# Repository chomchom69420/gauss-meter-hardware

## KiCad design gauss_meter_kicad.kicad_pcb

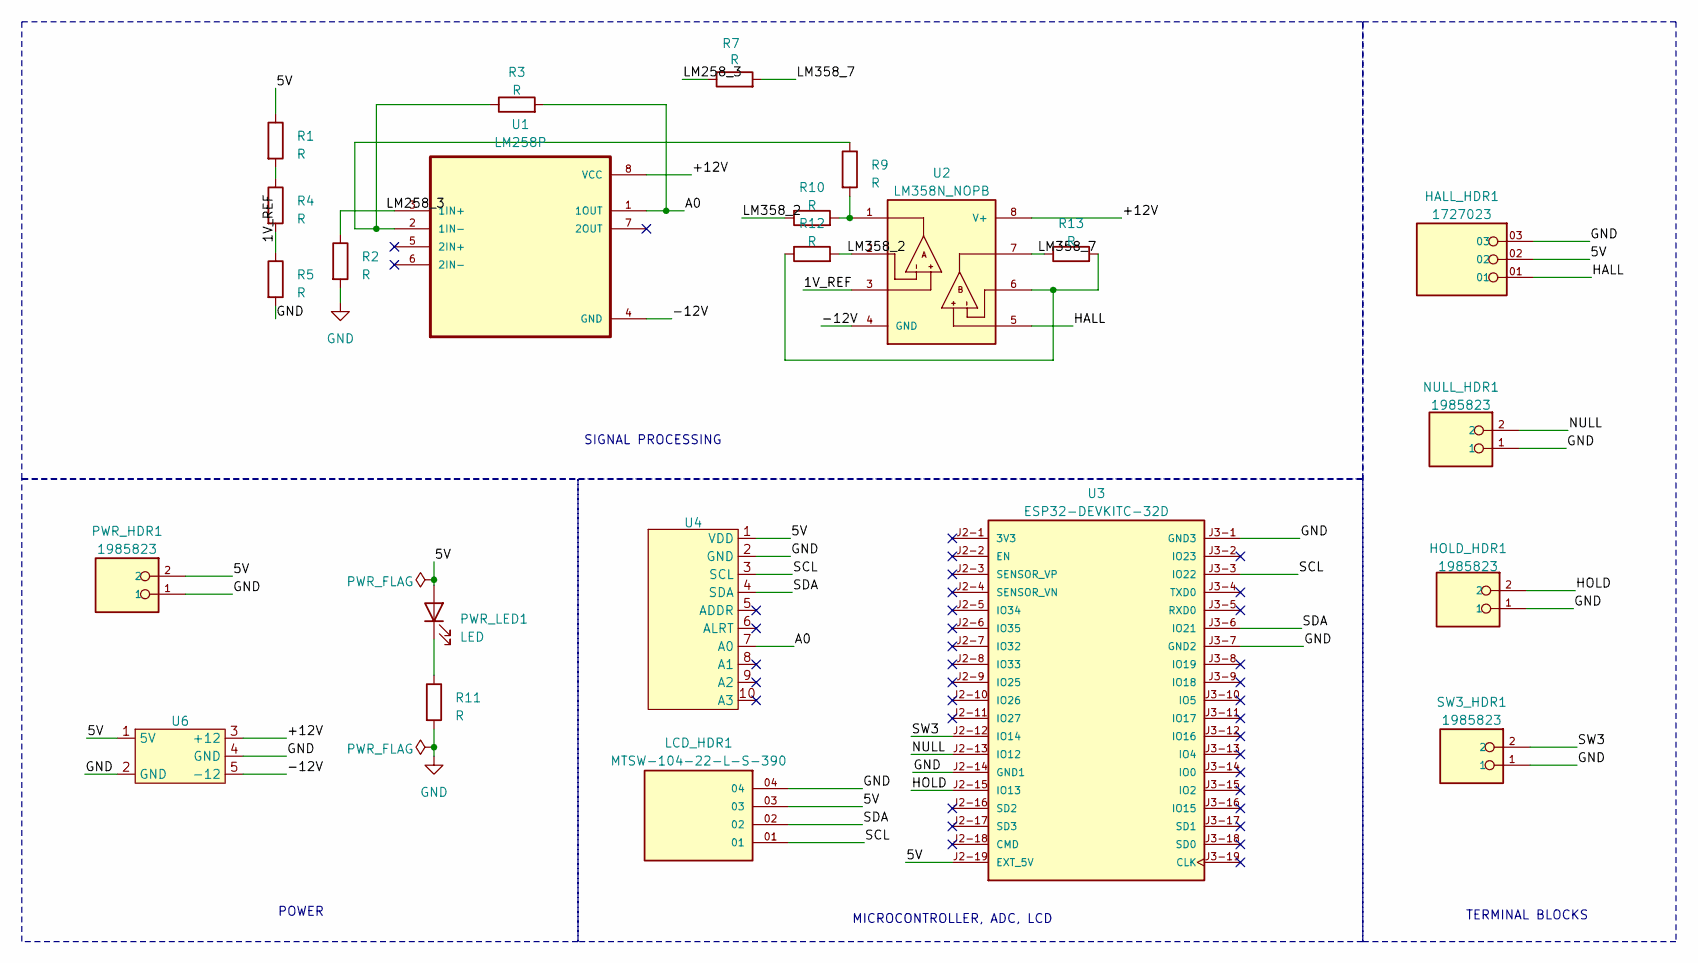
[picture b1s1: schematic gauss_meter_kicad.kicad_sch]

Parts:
HALL_HDR1: 1727023; PHOENIX_1727023; PARTREV 03.03.2021
HOLD_HDR1: 1985823; PHOENIX_1985823; PARTREV 03.03.2021
LCD_HDR1: MTSW-104-22-L-S-390; SAMTEC_MTSW-104-22-L-S-390; PARTREV R
NULL_HDR1: 1985823; PHOENIX_1985823; PARTREV 03.03.2021
PWR_HDR1: 1985823; PHOENIX_1985823; PARTREV 03.03.2021
PWR_LED1: LED; LED_D3.0mm_Horizontal_O1.27mm_Z2.0mm
R1, R2, R3, R4, R5, R7, R9, R10, R11, R12, R13: R; R_gauss_custom
SW3_HDR1: 1985823; PHOENIX_1985823; PARTREV 03.03.2021
U1: LM258P; DIP794W45P254L959H508Q8
U2: LM358N_NOPB; DIP794W45P254L959H508Q8
U3: ESP32-DEVKITC-32D; MODULE_ESP32-DEVKITC-32D; PARTREV V4
U4: ads1115
U6: DUAL_BOOST_5_12

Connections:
/1V_REF: R4.2, R5.1, U2.3
/5V: HALL_HDR1.02, LCD_HDR1.03, PWR_HDR1.2, PWR_LED1.2 (A), R1.1, U3.J2-19 (EXT_5V), U4.1 (VDD), U6.1 (5V)
/+12V: U1.8 (VCC), U2.8 (V+), U6.3 (+12)
/-12V: U1.4 (GND), U2.4 (GND), U6.5 (-12)
/A0: R3.2, U1.1 (1OUT), U4.7 (A0)
/HALL: HALL_HDR1.01, U2.5
/HOLD: HOLD_HDR1.2, U3.J2-15 (IO13)
/LM258_3: R2.1, R7.1, U1.3 (1IN+)
/LM358_2: R10.1, R12.2, U2.2
/LM358_7: R7.2, R13.1, U2.7
/NULL: NULL_HDR1.2, U3.J2-13 (IO12)
/SCL: LCD_HDR1.01, U3.J3-3 (IO22), U4.3 (SCL)
/SDA: LCD_HDR1.02, U3.J3-6 (IO21), U4.4 (SDA)
/SW3: SW3_HDR1.2, U3.J2-12 (IO14)
GND: HALL_HDR1.03, HOLD_HDR1.1, LCD_HDR1.04, NULL_HDR1.1, PWR_HDR1.1, R2.2, R5.2, R11.2, SW3_HDR1.1, U3.J2-14 (GND1), U3.J3-1 (GND3), U3.J3-7 (GND2), U4.2 (GND), U6.2 (GND), U6.4 (GND)
unnamed: PWR_LED1.1 (K), R11.1
unnamed: R1.2, R4.1
unnamed: R9.2, R10.2, U2.1
unnamed: R12.1, R13.2, U2.6
unnamed: R3.1, R9.1, U1.2 (1IN-)

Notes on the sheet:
POWER
MICROCONTROLLER, ADC, LCD
SIGNAL PROCESSING
TERMINAL BLOCKS

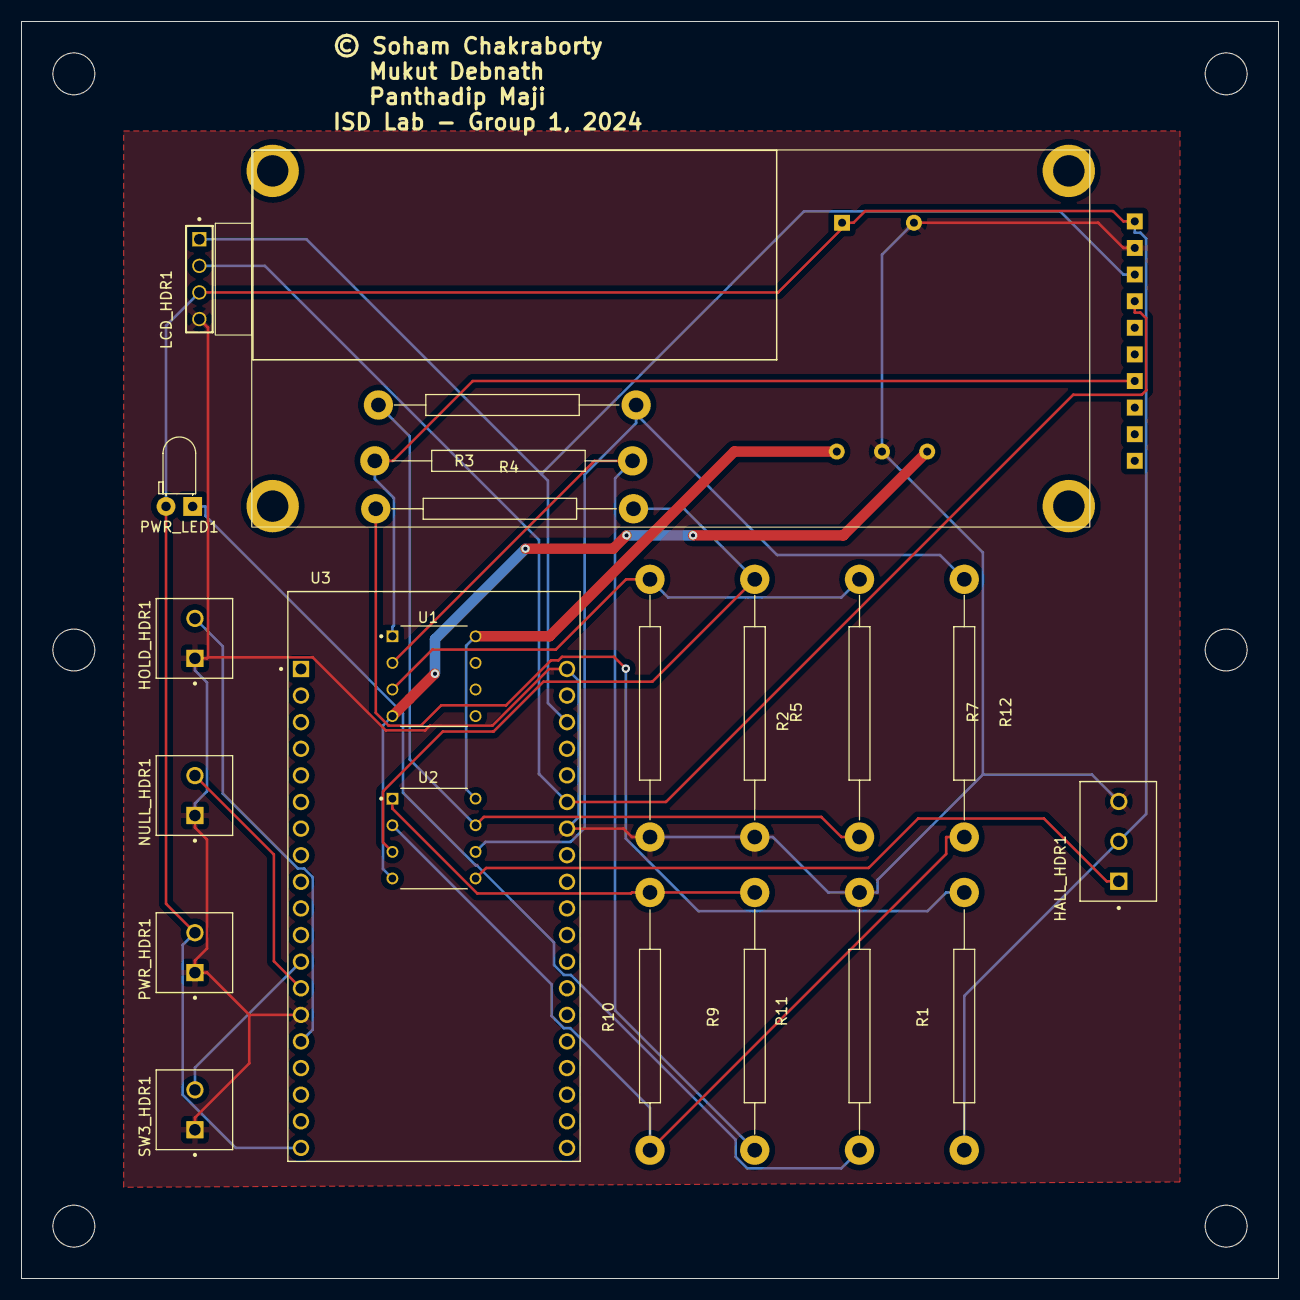
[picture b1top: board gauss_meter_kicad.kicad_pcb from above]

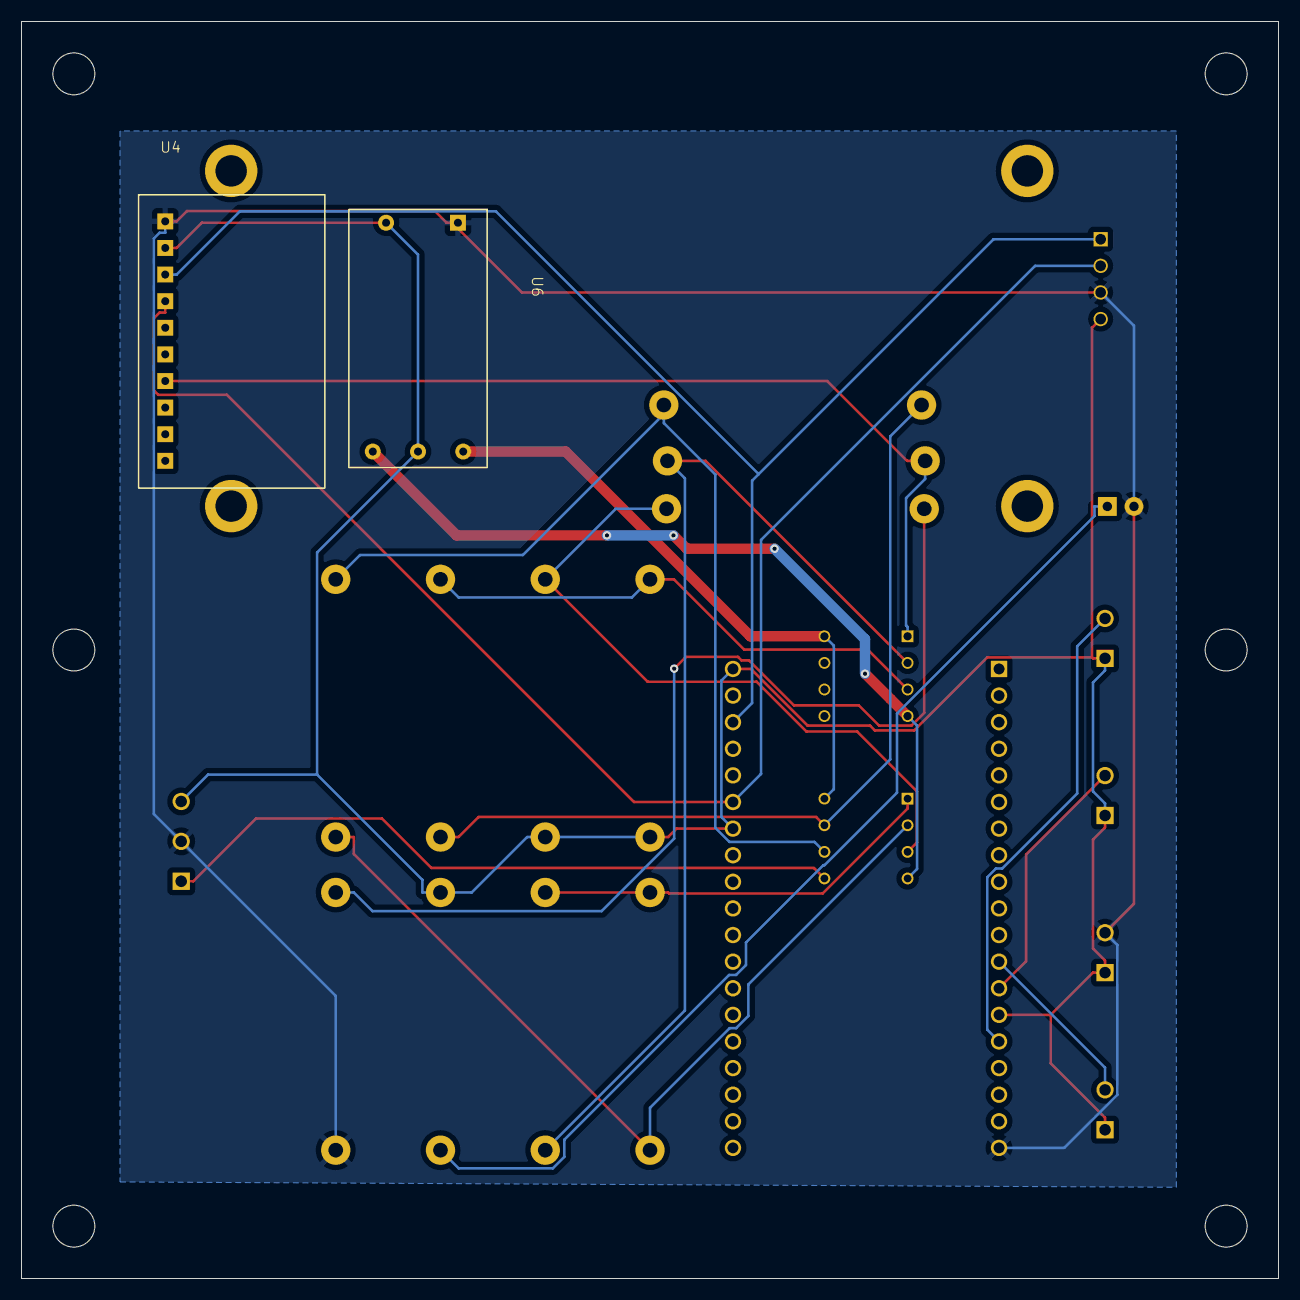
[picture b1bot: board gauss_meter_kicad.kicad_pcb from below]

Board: 2 copper layers, 120.0 x 120.0 mm, 23 parts (2 on the bottom side), 20 nets.

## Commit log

2024-03-19 added all
2024-03-19 finalized layout, generate gerber

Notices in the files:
gauss_meter_kicad.kicad_pcb:
© Soham Chakraborty
